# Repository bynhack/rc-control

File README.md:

# rc-control

**English** | [繁體中文](README.zh-TW.md) | [简体中文](README.zh-CN.md)

Drive RC cars with a sim-racing wheel and pedals. Plug the wheel into a 7" ESP32-P4 touch screen: it reads the wheel over USB, runs a driving model with ignition, gears, coasting and a real brake, and sends the result to the car over the radio that car uses. You don't need a PC.

## Features

- **Standalone wheel controller.** Built on the ESP32-P4 7" touch board with a MOZA R5 or Thrustmaster T300RS wheel base, picked on the screen.
- **Three ways to reach the car**, chosen per car:
  - ExpressLRS (CRSF)
  - a 4-in-1 MULTI module, over its serial protocol or as PPM
  - the toy car's own stock remote, with its pots driven by a DAC
- **Per-car handling** that every radio goes through. You set the steering range, expo, steering and throttle dead bands, trim, end points and reverse on the wheel itself.
- **Driving like a car.** Ignition, gears R N 1 2 3, coasting, a real brake, and an automatic brake-then-reverse sequence for the ESC.
- **Force feedback** on both bases (USB PID on the MOZA, Thrustmaster's protocol on the T300). Centring gets stronger with speed, and a soft stop marks the steering lock.
- **Dashboard.** Two instrument clusters with Simplified and Traditional Chinese text, six car profiles, and engine sound synthesised live on the board's speaker.
- **Desktop app** (Rust, optional). Drives an ELRS module from a PC and shows OpenIPC FPV video from a USB Wi-Fi adapter.
- **3D-printable parts and a car carrier board.** A stand for the MOZA base, mounts for the car, and a KiCad schematic.

## Documentation

| | |
|---|---|
| [Wheel controller](docs/en/wheel-controller.md) | Hardware, wiring, building and flashing the firmware |
| [Driving and handling](docs/en/driving.md) | Buttons, the driving model, cars, the handling settings, force feedback |
| [Radios](docs/en/radios.md) | ExpressLRS, MULTI 4-in-1, the toy remote |
| [Converting a toy remote](docs/en/toy-remote.md) | Driving a toy car's stock remote with an MCP4728 DAC |
| [Hardware](docs/en/hardware.md) | 3D-printed parts and the X2201 carrier board |
| [Desktop app](docs/en/desktop-app.md) | PC version: ELRS control, FPV video, Windows build |
| [Development](docs/en/development.md) | Code layout, serial console, tuning page, regenerating fonts and assets |

## Quick start

```bash
git clone https://github.com/bynhack/rc-control.git
cd rc-control/firmware/wheel-esp32
. ~/esp/esp-idf/export.sh          # ESP-IDF v5.5
idf.py build
idf.py -p /dev/cu.usbmodemXXXX flash
```

Then wire up a radio ([Radios](docs/en/radios.md)), plug the wheel into the board's USB-A port, and press Start on the wheel to start the engine.

## Repository layout

```
firmware/wheel-esp32/   the standalone controller (ESP-IDF, C)
  main/                 firmware source
  tools/                remote_tune.html, a Web Serial bench page
  enclosure/            3D-printable parts (Python, manifold3d)
  design/               the dashboard artwork
hardware/               boards (KiCad)
src/, native/           the desktop app (Rust, with C++ for the video link)
docs/                   documentation in three languages
```

## Contributing

Issues and pull requests are welcome. Before you open a pull request, build the firmware with `idf.py build`. If you touched the desktop app, also run `cargo test`. New documentation goes into all three languages under `docs/`. If you can only write one, say so in the pull request and someone will translate it.

## License

This project is released under **GPL-3.0-only** ([LICENSE](LICENSE)). That covers the desktop app, the firmware, the 3D models and the hardware design. If you distribute a modified version, including firmware flashed onto a device, you must offer its source under the same license.

Third-party code and assets keep their own licenses:

| Part | Where | License |
|---|---|---|
| [Aviateur](https://github.com/OpenIPC/aviateur) (FPV receive: devourer + wfb-ng) | `third_party/aviateur` (submodule) | GPL-3.0 |
| ffmpeg-sys-next 9.0.1, with Windows stubs added | `vendor/ffmpeg-sys-next-9.0.1` | WTFPL (FFmpeg itself is LGPL/GPL) |
| ESP-IDF usb_host_hid, with interrupt OUT reports added | `firmware/wheel-esp32/components/usb_host_hid` | Apache-2.0 |
| ESP-IDF, LVGL, the Waveshare BSP and other components | downloaded by the ESP-IDF component manager | Apache-2.0 / MIT etc. |
| Noto Sans SC, Saira, Barlow Condensed (rendered glyphs) | `firmware/wheel-esp32/main/fonts` | SIL Open Font License 1.1 |

MOZA, Thrustmaster, ExpressLRS, OpenIPC, Waveshare and other names only say which hardware works with this project. The project has no affiliation with them.

**Disclaimer:** RC cars are fast and heavy, and these modifications involve batteries and radio transmitters. You are responsible for any damage or injury that comes from following this project. Follow your local radio regulations.

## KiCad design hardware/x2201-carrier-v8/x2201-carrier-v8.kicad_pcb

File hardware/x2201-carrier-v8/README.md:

# X2201 載板 v8（ESP32-S3-MINI-1 + EP2）

46.3×34.5 mm，2 層，1.6 mm，單面零件，4 個 M2 不鍍銅孔（孔距 41.8×29.5）。

功能：**讓 EP2 上電就能工作、接線、電池電量偵測、計圈**，並接上圖傳 UART，供電量和圈速 OSD 使用。

接法：

- `電池 → 電調 → 馬達、舵機`（主電源，和原本一樣）
- `EP2 → PWM → 電調`：EP2 的 TX 焊盤是 S1（轉向），RX 焊盤是 S2（油門），經板子直接到 J1，不經過 S3，S3 當機也不影響開車
- `電調 BEC 5V → J1 → 板子`；EP2 的 5V 由 Q1 延遲約 0.5～1 秒才送出，等電調放開 EP2 的 TX 焊盤後再開機，這就是上電卡死的解法
- `電池 → Y 線 → J6`：細線分一路給電量偵測和圖傳，不是電調的主電源

EP2 要維持 **PWM 模式**。

## 手焊

只有 EP2，三種裝法擇一（不要同時用）：

- **焊盤朝上緣**：板上焊盤由左到右 G / 5V / RX / TX，天線朝板中央。
- **焊盤朝下**：板上焊盤由左到右 TX / RX / 5V / G，天線朝板子上緣，訊號通常較好。
- **插線**：EP2 接線到 J2，放到車上訊號好的位置。

貼板時 EP2 零件面朝上平放，四個半孔對齊焊盤（間距 2.4 mm），用烙鐵逐個點焊。**焊前依名稱核對 EP2 上的絲印，不要只看位置**。

## 接法

| 位號 | 類型 | 腳位 |
|---|---|---|
| J1 電調 | ZH1.5 4P | 1 S2 黃、2 S1 藍、3 GND 綠、4 5V 棕 |
| J2 EP2 外接 | ZH1.5 4P | 1 EP2 TX（S1）、2 EP2 RX（S2）、3 延遲 5V、4 GND |
| J3 圖傳 | SH1.0 6P | 1 電源、2 GND、3 圖傳 RX、4 圖傳 TX，5、6 不接 |
| J4 風扇 | ZH1.5 2P | 1 5V、2 GND，電調一開就轉 |
| J5 IR | ZH1.5 2P | 1 LED+、2 LED− |
| J6 電池 | ZH1.5 2P | 1 VBAT、2 GND |

電池的主線仍接電調。J6 用 Y 線分一路過來，供電壓偵測和圖傳使用；板子的 5V 由電調 BEC 經 J1 供給。
| J9 | USB-C | 燒錄與除錯 |

圖傳的電池電源由電調的 5V 控制（Q2、Q3）：電調開關關掉，圖傳也會斷電。

| GPIO | 功能 |
|---|---|
| 9 | 電池電壓（×22/122） |
| 10 / 11 | 圖傳 UART RX / TX |
| 15 | IR |

S3 不在控制鏈路上，空著的 GPIO 可以之後再用。

板子左上角的 B、G 兩個焊盤用來救磚：用鑷子短接 B 和 G，同時上電，就進入下載模式。

## 第一次上電

1. 電池先不接，插上電調線，從上往下看 J1 應是棕、綠、藍、黃。
2. 用萬用表確認 J6 的正負極。
3. 上電後 EP2 應在約 1 秒內開始閃燈，然後連上發射端。
4. D2、D3 隔開 USB 和電調 BEC，可以同時插。只插 USB 時，EP2、圖傳、風扇和 IR 都沒有電。

## 重新產生

```bash
/Applications/KiCad/KiCad.app/Contents/Frameworks/Python.framework/Versions/Current/bin/python3 gen_pcb.py
```

佈線用 `../tools/freerouting-1.9.0.jar`；沒有這個檔案時加 `REUSE_SES=1`，沿用已存的 `.ses`。`FAB=1` 同時輸出 Gerber、BOM 和座標檔，之後再跑 `gen_sch.py` 更新原理圖。

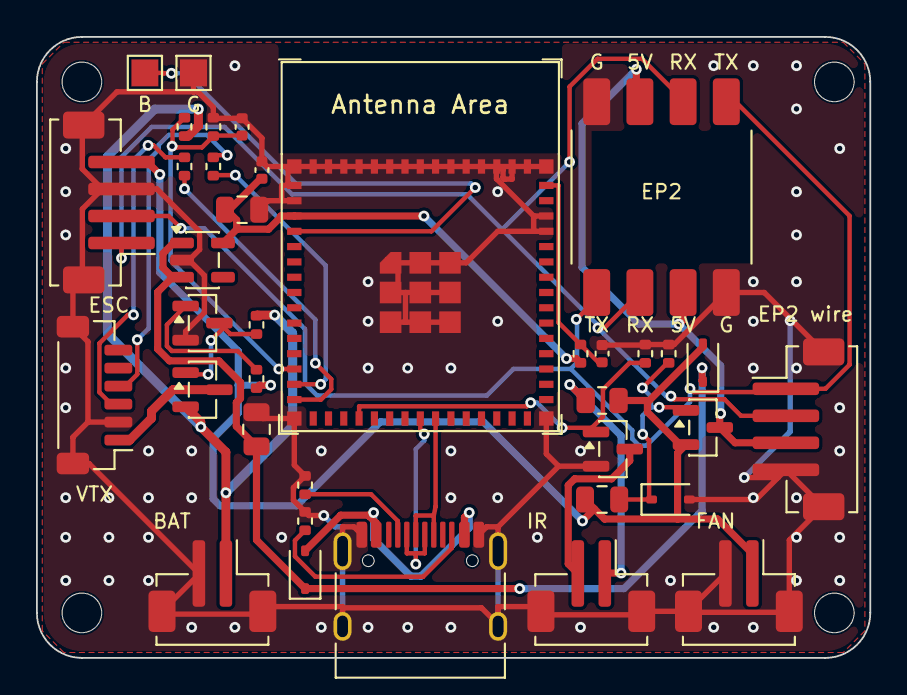
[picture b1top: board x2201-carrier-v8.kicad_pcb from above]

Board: 2 copper layers, 46.3 x 34.5 mm, 41 parts (0 on the bottom side), 27 nets.

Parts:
C1: 10uF; C_0805_2012Metric
C6, C11: 100nF; C_0402_1005Metric
C8: 1uF; C_0402_1005Metric
C9, C10: 22uF; C_0805_2012Metric
D1: 1N4148WS; D_SOD-323
D2, D3: B5819WS; D_SOD-323
J1: ZH1.5 4P (ESC); JST_ZH_B4B-ZR-SM4-TF_1x04-1MP_P1.50mm_Vertical
J2: ZH1.5 4P (EP2); JST_ZH_B4B-ZR-SM4-TF_1x04-1MP_P1.50mm_Vertical
J3: SH1.0 6P (VTX); JST_SH_BM06B-SRSS-TB_1x06-1MP_P1.00mm_Vertical
J4: ZH1.5 2P (fan); JST_ZH_B2B-ZR-SM4-TF_1x02-1MP_P1.50mm_Vertical
J5: ZH1.5 2P (IR LED); JST_ZH_B2B-ZR-SM4-TF_1x02-1MP_P1.50mm_Vertical
J6: ZH1.5 2P (battery); JST_ZH_B2B-ZR-SM4-TF_1x02-1MP_P1.50mm_Vertical
J9: USB-C; USB_C_Receptacle_HRO_TYPE-C-31-M-12
MH1, MH2, MH3, MH4: M2 hole
Q1, Q2: AO3401; SOT-23
Q3, Q4: AO3400; SOT-23
R1, R2, R8, R14: 100k; R_0402_1005Metric
R4, R19, R20: 1k; R_0402_1005Metric
R6: 33; R_0805_2012Metric
R12, R13: 5.1k; R_0402_1005Metric
R15: 22k; R_0402_1005Metric
R21: 10k; R_0402_1005Metric
TP1: BOOT; TestPoint_Pad_1.5x1.5mm
TP3: G; TestPoint_Pad_1.5x1.5mm
U1: ESP32-S3-MINI-1-N8; ESP32-S3-MINI-1
U2: EP2 2400RX; EP2_2400RX_SMD
U3: AP2112K-3.3; SOT-23-5

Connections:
3V3: C6.1, C10.1, R21.1, U1.3, U3.5
5V: C1.1, D3.2, J1.4, J4.1, Q1.2, R4.1, R6.2
BOOT: TP1.1, U1.4
CC1: J9.A5, R12.1
CC2: J9.B5, R13.1
EN: C8.1, R21.2, U1.45
GND: C6.2, C8.2, C9.2, C10.2, C11.2, D1.2, J1.3, J1.MP, J2.4, J2.MP, J3.2, J3.MP, J4.2, J4.MP, J5.MP, J6.2, J6.MP, J9.A1, J9.A12, J9.B1, J9.B12, J9.SH, Q3.2, Q4.2, R1.2, R8.2, R12.2, R13.2, R15.2, TP3.1, U1.1, U1.2, U1.42, U1.43, U1.46, U1.47, U1.48, U1.49, U1.50, U1.51, U1.52, U1.53, U1.54, U1.55, U1.56, U1.57, U1.58, U1.59, U1.60, U1.61, U1.62, U1.63, U1.64, U1.65, U2.G, U3.2
IR: Q4.1, R8.1, U1.19
LEDA: J5.1, R6.1
LEDK: J5.2, Q4.3
MSP_RX: R20.1, U1.14
MSP_TX: R19.1, U1.15
Q2G: Q2.1, Q3.3, R2.1
Q3G: Q3.1, R4.2
RX5V: J2.3, Q1.3, U2.5V
RXG: C1.2, D1.1, Q1.1, R1.1
S1: J1.2, J2.1, U2.TX
S2: J1.1, J2.2, U2.RX
USB_DM: J9.A7, J9.B7, U1.23
USB_DP: J9.A6, J9.B6, U1.24
VBAT: J6.1, Q2.2, R2.2, R14.1
VBAT_ADC: C11.1, R14.2, R15.1, U1.13
VBUS: D2.2, J9.A4, J9.A9, J9.B4, J9.B9
VIN: C9.1, D2.1, D3.1, U3.1, U3.3
VTX: J3.1, Q2.3
VTX_RX: J3.3, R19.2
VTX_TX: J3.4, R20.2

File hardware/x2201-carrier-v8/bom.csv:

Comment,Designator,Footprint,Qty,LCSC Part #
10uF,C1,C_0805_2012Metric,1,C15850
100nF,"C11,C6",C_0402_1005Metric,2,C1525
1uF,C8,C_0402_1005Metric,1,C52923
22uF,"C10,C9",C_0805_2012Metric,2,C45783
1N4148WS,D1,D_SOD-323,1,C2128
B5819WS,"D2,D3",D_SOD-323,2,C7420331
ZH1.5 4P (ESC),J1,JST_ZH_B4B-ZR-SM4-TF_1x04-1MP_P1.50mm_Vertical,1,C265083
ZH1.5 4P (EP2),J2,JST_ZH_B4B-ZR-SM4-TF_1x04-1MP_P1.50mm_Vertical,1,C265083
SH1.0 6P (VTX),J3,JST_SH_BM06B-SRSS-TB_1x06-1MP_P1.00mm_Vertical,1,C160392
ZH1.5 2P (fan),J4,JST_ZH_B2B-ZR-SM4-TF_1x02-1MP_P1.50mm_Vertical,1,C265284
ZH1.5 2P (IR LED),J5,JST_ZH_B2B-ZR-SM4-TF_1x02-1MP_P1.50mm_Vertical,1,C265284
ZH1.5 2P (battery),J6,JST_ZH_B2B-ZR-SM4-TF_1x02-1MP_P1.50mm_Vertical,1,C265284
USB-C,J9,USB_C_Receptacle_HRO_TYPE-C-31-M-12,1,C165948
AO3401,"Q1,Q2",SOT-23,2,C15127
AO3400,"Q3,Q4",SOT-23,2,C20917
5.1k,"R12,R13",R_0402_1005Metric,2,C25905
22k,R15,R_0402_1005Metric,1,C25768
10k,R21,R_0402_1005Metric,1,C25744
1k,"R19,R20,R4",R_0402_1005Metric,3,C11702
33,R6,R_0805_2012Metric,1,C17634
100k,"R1,R14,R2,R8",R_0402_1005Metric,4,C25741
ESP32-S3-MINI-1-N8,U1,ESP32-S3-MINI-1,1,C2913206
AP2112K-3.3,U3,SOT-23-5,1,C51118

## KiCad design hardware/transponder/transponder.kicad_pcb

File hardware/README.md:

# hardware

Boards for the cars (KiCad). 車上用的電路板 · 车上用的电路板

Where the boards are going: [ROADMAP.md](ROADMAP.md).

- [`x2201-carrier-v8`](x2201-carrier-v8): ESP32-S3-MINI-1 control board, on hold. The base for the next board.
- [`transponder`](transponder): the lap-timing transponder on its own, for the other cars.
- [`archive`](archive): v3 to v7, kept for reference.

Docs: [English](../docs/en/hardware.md#x2201-carrier-board) · [繁體中文](../docs/zh-TW/hardware.md#x2201-轉接板) · [简体中文](../docs/zh-CN/hardware.md#x2201-转接板)

`pcbgen.py` and `schgen.py` are the helpers the boards' `gen_pcb.py` / `gen_sch.py` share. `lib/` holds footprints and symbols KiCad doesn't ship: Espressif's ESP32-S3-MINI-1, and the SX1280, AT2401C and 2450FM07D0034 from AnyLeaf's elrs-hardware (MIT). See [lib/README.md](lib/README.md).

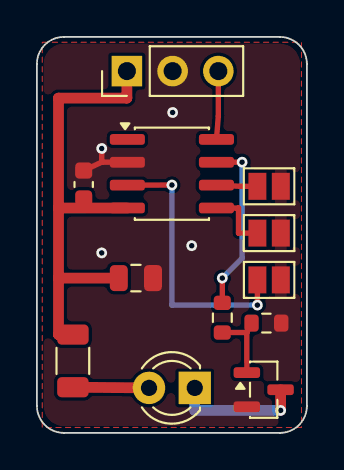
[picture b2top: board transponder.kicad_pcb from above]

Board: 2 copper layers, 15.0 x 22.0 mm, 12 parts (0 on the bottom side), 10 nets.

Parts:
C1: 100nF; C_0603_1608Metric
C2: 10uF; C_0805_2012Metric
D1: IR 940nm 3mm; LED_D3.0mm
J1: 5V GND SWIO; PinHeader_1x03_P2.54mm_Vertical
JP1: ID0; SolderJumper-2_P1.3mm_Open_Pad1.0x1.5mm
JP2: ID1; SolderJumper-2_P1.3mm_Open_Pad1.0x1.5mm
JP3: ID2; SolderJumper-2_P1.3mm_Open_Pad1.0x1.5mm
Q1: AO3400; SOT-23
R1: 33; R_1206_3216Metric
R2: 100; R_0603_1608Metric
R3: 100k; R_0603_1608Metric
U1: CH32V003J4M6; SOIC-8_3.9x4.9mm_P1.27mm

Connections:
5V: C1.2, C2.1, J1.1, R1.2, U1.4
GATE: Q1.1, R2.2, R3.1
GND: C1.1, C2.2, J1.2, JP1.2, JP2.2, JP3.2, Q1.2, R3.2, U1.2
ID0: JP1.1, U1.5
ID1: JP2.1, U1.6
ID2: JP3.1, U1.3
LEDA: D1.2, R1.1
LEDK: D1.1, Q1.3
PWM: R2.1, U1.7
SWIO: J1.3, U1.8

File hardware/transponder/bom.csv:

Comment,Designator,Footprint,Qty,LCSC Part #
100nF,C1,C_0603_1608Metric,1,C14663
10uF,C2,C_0805_2012Metric,1,C15850
AO3400,Q1,SOT-23,1,C20917
33,R1,R_1206_3216Metric,1,
100,R2,R_0603_1608Metric,1,C22775
100k,R3,R_0603_1608Metric,1,C25803
CH32V003J4M6,U1,SOIC-8_3.9x4.9mm_P1.27mm,1,C5299908

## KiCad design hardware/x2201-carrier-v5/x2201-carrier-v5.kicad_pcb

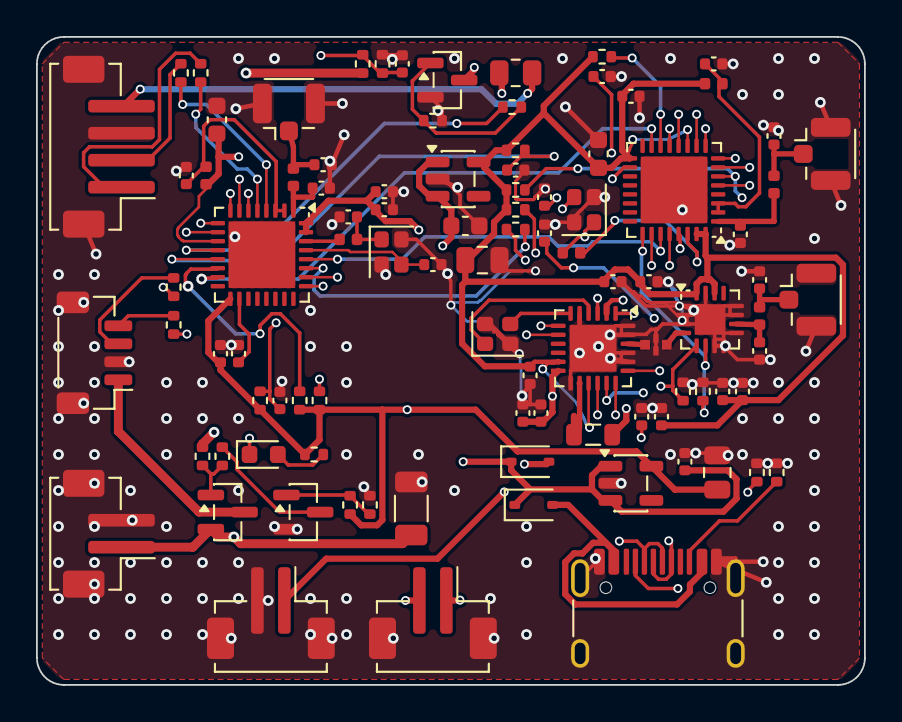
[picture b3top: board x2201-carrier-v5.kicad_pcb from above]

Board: 4 copper layers, 46.0 x 36.0 mm, 96 parts (0 on the bottom side), 70 nets.

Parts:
C3: 22uF 25V; C_1206_3216Metric
C8, C9, C18, C22, C25, C26, C42, C45, C49: 1uF; C_0402_1005Metric
C10, C17: 22uF; C_0805_2012Metric
C11, C21, C34, C35, C36, C44: 100nF; C_0402_1005Metric
C16: 1uF; C_0603_1608Metric
C19, C31, C33, C46: 10nF; C_0402_1005Metric
C20, C43: 10uF; C_0603_1608Metric
C27, C28, C37, C50, C51: 10pF; C_0402_1005Metric
C29, C30, C38, C39, C40, C41: 1.2pF; C_0402_1005Metric
C32: 470nF; C_0402_1005Metric
D2, D3: B5819WS; D_SOD-323
D4: green; LED_0603_1608Metric
FL1: 2450FM07D0034T; 2450FM07D0034
J1: ZH1.5 4P (ESC); JST_ZH_B4B-ZR-SM4-TF_1x04-1MP_P1.50mm_Vertical
J3: SH1.0 4P (VTX); JST_SH_BM04B-SRSS-TB_1x04-1MP_P1.00mm_Vertical
J4: ZH1.5 2P (fan); JST_ZH_B2B-ZR-SM4-TF_1x02-1MP_P1.50mm_Vertical
J5: ZH1.5 2P (IR LED); JST_ZH_B2B-ZR-SM4-TF_1x02-1MP_P1.50mm_Vertical
J6: ZH1.5 2P (battery); JST_ZH_B2B-ZR-SM4-TF_1x02-1MP_P1.50mm_Vertical
J9: USB-C; USB_C_Receptacle_HRO_TYPE-C-31-M-12
J10: U.FL (ELRS); U.FL_Hirose_U.FL-R-SMT-1_Vertical
J11: U.FL (receiver WiFi); U.FL_Hirose_U.FL-R-SMT-1_Vertical
J12: U.FL (brain WiFi); U.FL_Hirose_U.FL-R-SMT-1_Vertical
L2, L8: 2nH; L_0402_1005Metric
L3, L9: 24nH; L_0402_1005Metric
L4, L6, L7: 3nH; L_0402_1005Metric
L5: 15uH; L_0805_2012Metric
Q2: AO3401; SOT-23
Q3, Q4: AO3400; SOT-23
R2, R5, R8, R14, R31, R32: 100k; R_0402_1005Metric
R3: 47k; R_0402_1005Metric
R4, R18, R19, R20, R30: 1k; R_0402_1005Metric
R6: 33; R_0805_2012Metric
R7: 100; R_0402_1005Metric
R11, R25, R26, R27, R28, R29, R34: 10k; R_0402_1005Metric
R12, R13: 5.1k; R_0402_1005Metric
R15: 22k; R_0402_1005Metric
R16, R17: 220; R_0402_1005Metric
U1, U5: ESP32-C3FH4; QFN-32-1EP_5x5mm_P0.5mm_EP3.7x3.7mm
U3, U8: AP2112K-3.3; SOT-23-5
U6: SX1280IMLTRT; QFN-24-1EP_4x4mm_P0.5mm_EP2.6x2.6mm
U7: AT2401C; QFN-16-1EP_3x3mm_P0.5mm_EP1.7x1.7mm
Y1, Y3: 40MHz; Crystal_SMD_2016-4Pin_2.0x1.6mm
Y2: 52MHz; Crystal_SMD_2016-4Pin_2.0x1.6mm

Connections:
3V3: C10.1, C43.1, C44.1, C45.1, C46.1, L8.1, R4.1, R11.1, R18.1, R25.1, R34.1, U1.11, U1.17, U1.31, U1.32, U3.5
3V3R: C17.1, C18.1, C19.1, C20.1, C21.1, C34.1, C35.1, C36.1, C37.1, L2.1, R26.1, R27.1, R28.1, R29.1, U5.11, U5.17, U5.31, U5.32, U6.11, U6.15, U7.14, U7.16, U8.5
5V: D3.2, J1.4, J4.1, R6.2
B_ANT: C41.1, J12.1, L7.2
B_IO2: R25.2, U1.6
B_RF: C40.1, L7.1, U1.1
B_VPA: C42.1, L8.2, U1.2, U1.3
B_VSPI: C49.1, U1.18
B_XI: C51.1, L9.1, Y3.1
B_XN: C50.1, U1.29, Y3.3
B_XP: L9.2, U1.30
CC1: J9.A5, R12.1
CC2: J9.B5, R13.1
CRSF_RX: R30.2, U1.27
CRSF_TX: U1.28, U5.27
ELRS_ANT: C39.1, J10.1, L6.2
EN: C8.1, R11.2, U1.7
GATE: Q4.1, R7.2, R8.1
GND: C3.2, C8.2, C9.2, C10.2, C11.2, C16.2, C17.2, C18.2, C19.2, C20.2, C21.2, C22.2, C25.2, C26.2, C27.2, C28.2, C29.2, C30.2, C31.2, C32.2, C33.2, C34.2, C35.2, C36.2, C37.2, C38.2, C39.2, C40.2, C41.2, C42.2, C43.2, C44.2, C45.2, C46.2, C49.2, C50.2, C51.2, FL1.2, FL1.4, J1.3, J1.MP, J3.2, J3.MP, J4.2, J4.MP, J5.MP, J6.2, J6.MP, J9.A1, J9.A12, J9.B1, J9.B12, J9.SH, J10.2, J11.2, J12.2, Q3.2, Q4.2, R5.2, R8.2, R12.2, R13.2, R15.2, R31.2, R32.2, U1.33, U3.2, U5.33, U6.5, U6.13, U6.20, U6.21, U6.23, U6.24, U6.25, U7.1, U7.2, U7.3, U7.7, U7.8, U7.9, U7.11, U7.12, U7.15, U7.17, U8.2, Y1.2, Y1.4, Y2.2, Y2.4, Y3.2, Y3.4
IR: R7.1, U1.12
LED: D4.1, R34.2, U1.14
LEDA: J5.1, R6.1
LEDK: J5.2, Q4.3
LEDR: D4.2, R18.2
MSP_RX: R20.1, U1.10
MSP_TX: R19.1, U1.9
PA_ANT: C38.1, L6.1, U7.10
PA_IO: FL1.3, U7.4
PA_RXEN: R32.1, U5.25, U7.6
PA_TXEN: R31.1, U5.26, U7.5
Q2G: Q2.1, R2.1, R3.1
Q3D: Q3.3, R3.2
Q3G: Q3.1, R4.2, R5.1
RXC_ANT: C30.1, J11.1, L4.2
RXC_BOOT: R29.2, U1.15, U5.15
RXC_EN: C26.1, R26.2, U1.13, U5.7
RXC_IO8: R28.2, U5.14
RXC_RF: C29.1, L4.1, U5.1
RXC_TXD: R30.1, U5.28
RXC_VPA: C22.1, L2.2, U5.2, U5.3
RXC_VSPI: C25.1, U5.18
RXC_XI: C27.1, L3.1, Y1.1
RXC_XN: C28.1, U5.29, Y1.3
RXC_XP: L3.2, U5.30
RX_BUSY: U5.8, U6.7
RX_DIO1: U5.5, U6.8
RX_MISO: U5.10, U6.16
RX_MOSI: U5.9, U6.17
RX_NSS: U5.13, U6.19
RX_RST: R27.2, U5.6, U6.3
RX_SCK: U5.12, U6.18
S1: R16.1, U1.4
S1E: J1.2, R16.2
S2: R17.1, U1.5
S2E: J1.1, R17.2
SX_DCC: C32.1, C33.1, L5.2, U6.2, U6.12
SX_RF: FL1.1, U6.22
SX_SW: L5.1, U6.14
SX_VRPA: C31.1, U6.1
SX_XA: U6.4, Y2.1
SX_XB: U6.6, Y2.3
USB_DM: J9.A7, J9.B7, U1.25
USB_DP: J9.A6, J9.B6, U1.26
VBAT: C3.1, J6.1, Q2.2, R2.2, R14.1
VBAT_ADC: C11.1, R14.2, R15.1, U1.8
VBUS: D2.2, J9.A4, J9.A9, J9.B4, J9.B9
VIN: C9.1, C16.1, D2.1, D3.1, U3.1, U3.3, U8.1, U8.3
VTX: J3.1, Q2.3
VTX_RX: J3.3, R19.2
VTX_TX: J3.4, R20.2

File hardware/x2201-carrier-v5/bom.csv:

Comment,Designator,Footprint,Qty,LCSC Part #
22uF,"C10,C17",C_0805_2012Metric,2,C45783
1uF,C16,C_0603_1608Metric,1,C15849
22uF 25V,C3,C_1206_3216Metric,1,C12891
470nF,C32,C_0402_1005Metric,1,C47339
1.2pF,"C29,C30,C38,C39,C40,C41",C_0402_1005Metric,6,C327292
10uF,"C20,C43",C_0603_1608Metric,2,C19702
100nF,"C11,C21,C34,C35,C36,C44",C_0402_1005Metric,6,C1525
10nF,"C19,C31,C33,C46",C_0402_1005Metric,4,C15195
10pF,"C27,C28,C37,C50,C51",C_0402_1005Metric,5,C32949
1uF,"C18,C22,C25,C26,C42,C45,C49,C8,C9",C_0402_1005Metric,9,C52923
B5819WS,"D2,D3",D_SOD-323,2,C7420331
green,D4,LED_0603_1608Metric,1,C72043
2450FM07D0034T,FL1,2450FM07D0034,1,C2651081
ZH1.5 4P (ESC),J1,JST_ZH_B4B-ZR-SM4-TF_1x04-1MP_P1.50mm_Vertical,1,C265083
U.FL (ELRS),J10,U.FL_Hirose_U.FL-R-SMT-1_Vertical,1,C88374
U.FL (receiver WiFi),J11,U.FL_Hirose_U.FL-R-SMT-1_Vertical,1,C88374
U.FL (brain WiFi),J12,U.FL_Hirose_U.FL-R-SMT-1_Vertical,1,C88374
SH1.0 4P (VTX),J3,JST_SH_BM04B-SRSS-TB_1x04-1MP_P1.00mm_Vertical,1,C160390
ZH1.5 2P (fan),J4,JST_ZH_B2B-ZR-SM4-TF_1x02-1MP_P1.50mm_Vertical,1,C265284
ZH1.5 2P (IR LED),J5,JST_ZH_B2B-ZR-SM4-TF_1x02-1MP_P1.50mm_Vertical,1,C265284
ZH1.5 2P (battery),J6,JST_ZH_B2B-ZR-SM4-TF_1x02-1MP_P1.50mm_Vertical,1,C265284
USB-C,J9,USB_C_Receptacle_HRO_TYPE-C-31-M-12,1,C165948
15uH,L5,L_0805_2012Metric,1,C486333
3nH,"L4,L6,L7",L_0402_1005Metric,3,C269824
2nH,"L2,L8",L_0402_1005Metric,2,C43365
24nH,"L3,L9",L_0402_1005Metric,2,C74301
AO3401,Q2,SOT-23,1,C15127
AO3400,"Q3,Q4",SOT-23,2,C20917
5.1k,"R12,R13",R_0402_1005Metric,2,C25905
22k,R15,R_0402_1005Metric,1,C25768
220,"R16,R17",R_0402_1005Metric,2,C25091
1k,"R18,R19,R20,R30,R4",R_0402_1005Metric,5,C11702
47k,R3,R_0402_1005Metric,1,C25792
10k,"R11,R25,R26,R27,R28,R29,R34",R_0402_1005Metric,7,C25744
33,R6,R_0805_2012Metric,1,C17634
100,R7,R_0402_1005Metric,1,C25076
100k,"R14,R2,R31,R32,R5,R8",R_0402_1005Metric,6,C25741
ESP32-C3FH4,"U1,U5",QFN-32-1EP_5x5mm_P0.5mm_EP3.7x3.7mm,2,C2858491
AP2112K-3.3,"U3,U8",SOT-23-5,2,C51118
SX1280IMLTRT,U6,QFN-24-1EP_4x4mm_P0.5mm_EP2.6x2.6mm,1,C125969
AT2401C,U7,QFN-16-1EP_3x3mm_P0.5mm_EP1.7x1.7mm,1,C783588
52MHz,Y2,Crystal_SMD_2016-4Pin_2.0x1.6mm,1,C841202
40MHz,"Y1,Y3",Crystal_SMD_2016-4Pin_2.0x1.6mm,2,C49158179

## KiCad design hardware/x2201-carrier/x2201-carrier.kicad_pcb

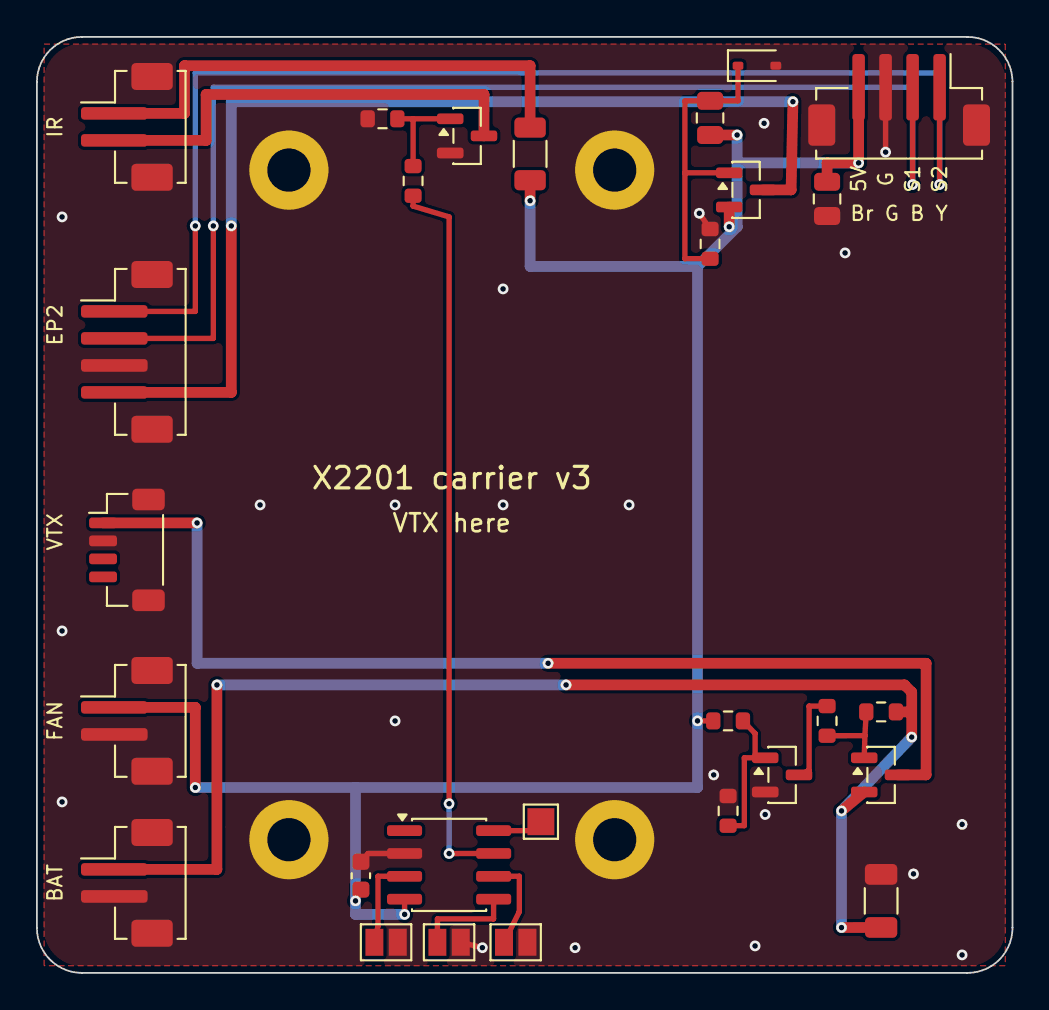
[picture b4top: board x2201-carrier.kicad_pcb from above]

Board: 2 copper layers, 54.2 x 52.0 mm, 32 parts (0 on the bottom side), 19 nets.

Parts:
C1: 10uF; C_0805_2012Metric
C2: 22uF; C_0805_2012Metric
C3: 22uF 25V; C_1206_3216Metric
C4: 100nF; C_0603_1608Metric
D1: 1N4148WS; D_SOD-323
H1, H2, H3, H4: M2 SMT nut
J1: ZH1.5 4P (ESC); JST_ZH_B4B-ZR-SM4-TF_1x04-1MP_P1.50mm_Vertical
J2: ZH1.5 4P (EP2); JST_ZH_B4B-ZR-SM4-TF_1x04-1MP_P1.50mm_Vertical
J3: SH1.0 4P (VTX); JST_SH_BM04B-SRSS-TB_1x04-1MP_P1.00mm_Vertical
J4: ZH1.5 2P (fan); JST_ZH_B2B-ZR-SM4-TF_1x02-1MP_P1.50mm_Vertical
J5: ZH1.5 2P (IR LED); JST_ZH_B2B-ZR-SM4-TF_1x02-1MP_P1.50mm_Vertical
J6: ZH1.5 2P (battery); JST_ZH_B2B-ZR-SM4-TF_1x02-1MP_P1.50mm_Vertical
JP1: ID0; SolderJumper-2_P1.3mm_Open_Pad1.0x1.5mm
JP2: ID1; SolderJumper-2_P1.3mm_Open_Pad1.0x1.5mm
JP3: ID2; SolderJumper-2_P1.3mm_Open_Pad1.0x1.5mm
Q1, Q2: AO3401; SOT-23
Q3, Q4: AO3400; SOT-23
R1, R2, R5, R8: 100k; R_0603_1608Metric
R3: 47k; R_0603_1608Metric
R4: 1k; R_0603_1608Metric
R6: 33; R_1206_3216Metric
R7: 100; R_0603_1608Metric
TP11: SWIO; TestPoint_Pad_1.5x1.5mm
U2: CH32V003J4M6; SOIC-8_3.9x4.9mm_P1.27mm

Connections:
5V: C1.1, C2.1, C4.2, J1.4, J4.1, Q1.2, R4.1, R6.2, U2.4
GATE: Q4.1, R7.2, R8.2
GND: C2.2, C3.2, C4.1, D1.2, H1.1, H2.1, H3.1, H4.1, J1.3, J1.MP, J2.3, J2.MP, J3.2, J3.MP, J4.2, J4.MP, J5.MP, J6.2, J6.MP, JP1.2, JP2.2, JP3.2, Q3.2, Q4.2, R1.2, R5.2, R8.1, U2.2
ID0: JP1.1, U2.5
ID1: JP2.1, U2.6
ID2: JP3.1, U2.3
LEDA: J5.1, R6.1
LEDK: J5.2, Q4.3
PWM: R7.1, U2.7
Q2G: Q2.1, R2.1, R3.1
Q3D: Q3.3, R3.2
Q3G: Q3.1, R4.2, R5.1
RX5V: J2.4, Q1.3
RXG: C1.2, D1.1, Q1.1, R1.1
S1: J1.2, J2.2
S2: J1.1, J2.1
SWIO: TP11.1, U2.8
VBAT: C3.1, J6.1, Q2.2, R2.2
VTX: J3.1, Q2.3

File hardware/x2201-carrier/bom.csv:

Comment,Designator,Footprint,Qty,LCSC Part #
10uF,C1,C_0805_2012Metric,1,C15850
22uF,C2,C_0805_2012Metric,1,C45783
22uF 25V,C3,C_1206_3216Metric,1,C12891
100nF,C4,C_0603_1608Metric,1,C14663
1N4148WS,D1,D_SOD-323,1,C2128
M2 SMT nut,"H1,H2,H3,H4",,4,
ZH1.5 4P (ESC),J1,JST_ZH_B4B-ZR-SM4-TF_1x04-1MP_P1.50mm_Vertical,1,C265083
ZH1.5 4P (EP2),J2,JST_ZH_B4B-ZR-SM4-TF_1x04-1MP_P1.50mm_Vertical,1,C265083
SH1.0 4P (VTX),J3,JST_SH_BM04B-SRSS-TB_1x04-1MP_P1.00mm_Vertical,1,C160390
ZH1.5 2P (fan),J4,JST_ZH_B2B-ZR-SM4-TF_1x02-1MP_P1.50mm_Vertical,1,C265284
ZH1.5 2P (IR LED),J5,JST_ZH_B2B-ZR-SM4-TF_1x02-1MP_P1.50mm_Vertical,1,C265284
ZH1.5 2P (battery),J6,JST_ZH_B2B-ZR-SM4-TF_1x02-1MP_P1.50mm_Vertical,1,C265284
AO3401,"Q1,Q2",SOT-23,2,C15127
AO3400,"Q3,Q4",SOT-23,2,C20917
47k,R3,R_0603_1608Metric,1,C25819
1k,R4,R_0603_1608Metric,1,C21190
33,R6,R_1206_3216Metric,1,
100,R7,R_0603_1608Metric,1,C22775
100k,"R1,R2,R5,R8",R_0603_1608Metric,4,C25803
CH32V003J4M6,U2,SOIC-8_3.9x4.9mm_P1.27mm,1,C5299908

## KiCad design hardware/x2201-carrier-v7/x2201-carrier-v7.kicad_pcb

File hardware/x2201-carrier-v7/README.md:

# X2201 載板 v7（ESP32-S3-Zero + EP2）

47×30 mm，2 層，1.6 mm，單面零件，4 個 M2 不鍍銅孔（孔距 42×25）。

只做這些事：**電池電量偵測、計圈、讓 EP2 上電就能工作、接線**，並接上圖傳 UART，供之後做 OSD。

訊號鏈：`EP2 → CRSF → S3-Zero → PWM → 電調`。EP2 不再直接接電調，R11 再把它的 TX 腳拉高，這就是上電卡死的解法。

## 下單

| 項目 | 內容 |
|---|---|
| PCB | 上傳 `x2201-carrier-v7-gerber.zip`：2 層、1.6 mm、1 oz |
| 元件 | `bom.csv` 上的料號，全部可在立創商城買到 |
| 模組 | ESP32-S3-Zero、EP2 2400RX 各一 |
| 插頭線 | ZH1.5 4P ×1、ZH1.5 2P ×3（圖傳用它原裝的 SH1.0 線） |

## 手焊順序

位置看 `x2201-carrier-v7-assembly.png`，零件編號對照 `bom.csv`。

1. MOS（Q2 是 AO3401，Q3、Q4 是 AO3400）和二極體 D3。
2. 所有 0805 阻容。
3. 插座：先焊 J3（SH1.0，腳距最小），再焊 J1、J4、J5、J6。
4. 先量：5V、VBAT、3V3 對 GND 都不能短路。
5. 焊 S3-Zero：USB 朝板邊，對齊 18 個焊盤。
6. 焊 EP2：貼在絲印框內，四個焊盤用短線橋接到板上 TX / RX / 5V / G，**依名稱對應，不要只看位置**。

## 接法

| 位號 | 類型 | 腳位 |
|---|---|---|
| J1 電調 | ZH1.5 4P | 1 S2 黃、2 S1 藍、3 GND 綠、4 5V 棕 |
| J3 圖傳 | SH1.0 4P | 1 電源、2 GND、3 圖傳 RX、4 圖傳 TX |
| J4 風扇 | ZH1.5 2P | 1 5V、2 GND，電調一開就轉 |
| J5 IR | ZH1.5 2P | 1 LED+、2 LED− |
| J6 電池 | ZH1.5 2P | 1 VBAT、2 GND |

圖傳的電池電源由電調的 5V 控制（Q2、Q3）：電調開關關掉，圖傳也會斷電。

| GPIO | 功能 |
|---|---|
| 4 | IR |
| 5 / 6 | CRSF RX / TX |
| 7 / 8 | 電調 S2 / S1 |
| 9 | 電池電壓（×22/122） |
| 11 / 12 | 圖傳 UART TX / RX（MSP OSD） |

## 第一次上電

上電測試在 [firmware/elrs-bench](../../firmware/elrs-bench/README.md)，韌體的接腳和這塊板相同。

- D3 會擋住 USB 流進電調 BEC，焊好後可以同時插 USB 和電調。
- J1 的線序（第 1 腳是 S2）還要對照實車確認。

## 重新產生

```bash
/Applications/KiCad/KiCad.app/Contents/Frameworks/Python.framework/Versions/Current/bin/python3 gen_pcb.py
```

佈線用 `../tools/freerouting-1.9.0.jar`；沒有這個檔案時加 `REUSE_SES=1`，沿用已存的 `.ses`。`FAB=1` 同時輸出 Gerber 和 BOM，之後再跑 `gen_sch.py` 更新原理圖。

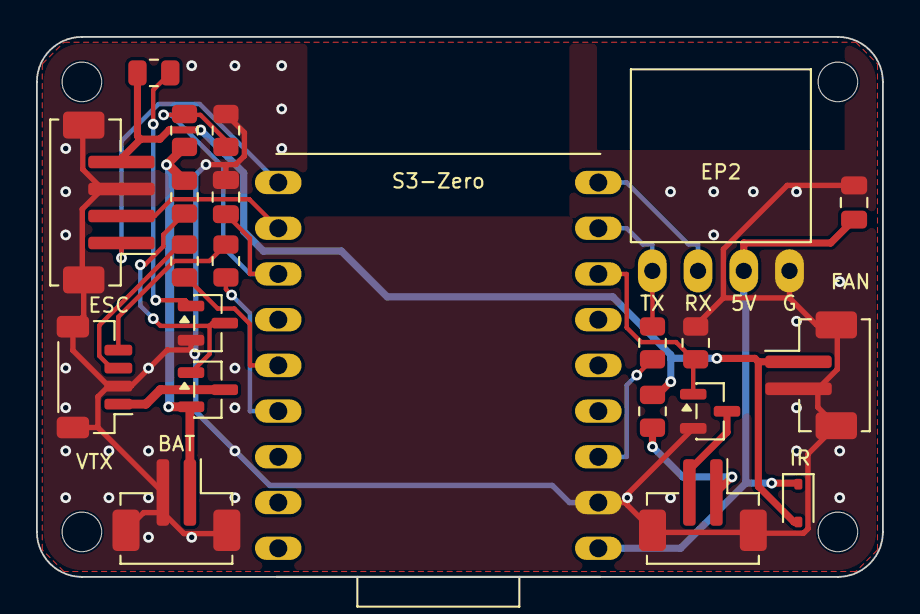
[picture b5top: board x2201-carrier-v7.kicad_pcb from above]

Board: 2 copper layers, 47.0 x 30.0 mm, 26 parts (0 on the bottom side), 20 nets.

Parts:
C10: 22uF; C_0805_2012Metric
C11: 100nF; C_0805_2012Metric
D3: B5819WS; D_SOD-323
J1: ZH1.5 4P (ESC); JST_ZH_B4B-ZR-SM4-TF_1x04-1MP_P1.50mm_Vertical
J3: SH1.0 4P (VTX); JST_SH_BM04B-SRSS-TB_1x04-1MP_P1.00mm_Vertical
J4: ZH1.5 2P (fan); JST_ZH_B2B-ZR-SM4-TF_1x02-1MP_P1.50mm_Vertical
J5: ZH1.5 2P (IR LED); JST_ZH_B2B-ZR-SM4-TF_1x02-1MP_P1.50mm_Vertical
J6: ZH1.5 2P (battery); JST_ZH_B2B-ZR-SM4-TF_1x02-1MP_P1.50mm_Vertical
MH1, MH2, MH3, MH4: M2 hole
Q2: AO3401; SOT-23
Q3, Q4: AO3400; SOT-23
R2, R8, R14: 100k; R_0805_2012Metric
R4, R19, R20: 1k; R_0805_2012Metric
R6: 33; R_0805_2012Metric
R11: 10k; R_0805_2012Metric
R15: 22k; R_0805_2012Metric
U1: ESP32-S3-Zero
U2: EP2 2400RX; EP2_2400RX

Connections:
3V3: R11.1, U1.3V3
5V: D3.2, J1.4, J4.1, R4.1, R6.2
5VM: C10.1, D3.1, U1.5V, U2.5V
CRSF_RX: R11.2, U1.5, U2.TX
CRSF_TX: U1.6, U2.RX
GND: C10.2, C11.2, J1.3, J1.MP, J3.2, J3.MP, J4.2, J4.MP, J5.MP, J6.2, J6.MP, Q3.2, Q4.2, R8.2, R15.2, U1.GND, U2.G
IR: Q4.1, R8.1, U1.4
LEDA: J5.1, R6.1
LEDK: J5.2, Q4.3
MSP_RX: R20.1, U1.12
MSP_TX: R19.1, U1.11
Q2G: Q2.1, Q3.3, R2.1
Q3G: Q3.1, R4.2
S1: J1.2, U1.8
S2: J1.1, U1.7
VBAT: J6.1, Q2.2, R2.2, R14.1
VBAT_ADC: C11.1, R14.2, R15.1, U1.9
VTX: J3.1, Q2.3
VTX_RX: J3.3, R19.2
VTX_TX: J3.4, R20.2

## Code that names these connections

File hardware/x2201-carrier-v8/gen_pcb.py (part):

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
# ---- U1: ESP32-S3-MINI-1, antenna at the top edge ------------------------------------------
CX, CY = 21.3, 14.2
GPIO = {3: "3V3", 4: "BOOT", 13: "VBAT_ADC", 14: "MSP_RX", 15: "MSP_TX",  # left column: IO9..IO11
        19: "IR", 23: "USB_DM", 24: "USB_DP", 45: "EN"}  # bottom row: IO15, USB
U1_NETS = {str(k): v for k, v in GPIO.items()}
for n in (1, 2, 42, 43, *range(46, 66)):
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

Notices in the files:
parts and their libraries:
From AnyLeaf elrs-hardware (MIT, (c) 2023 AnyLeaf LLC). https://www.johansontechnology.com/datasheets/2450FM07D0034/2450FM07D0034.pdf
